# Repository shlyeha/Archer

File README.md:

# Nasty clock crack
Archer is a crack system for nasty gps-clock that makes it possible to 
sleep when you are on duty in a responsible position

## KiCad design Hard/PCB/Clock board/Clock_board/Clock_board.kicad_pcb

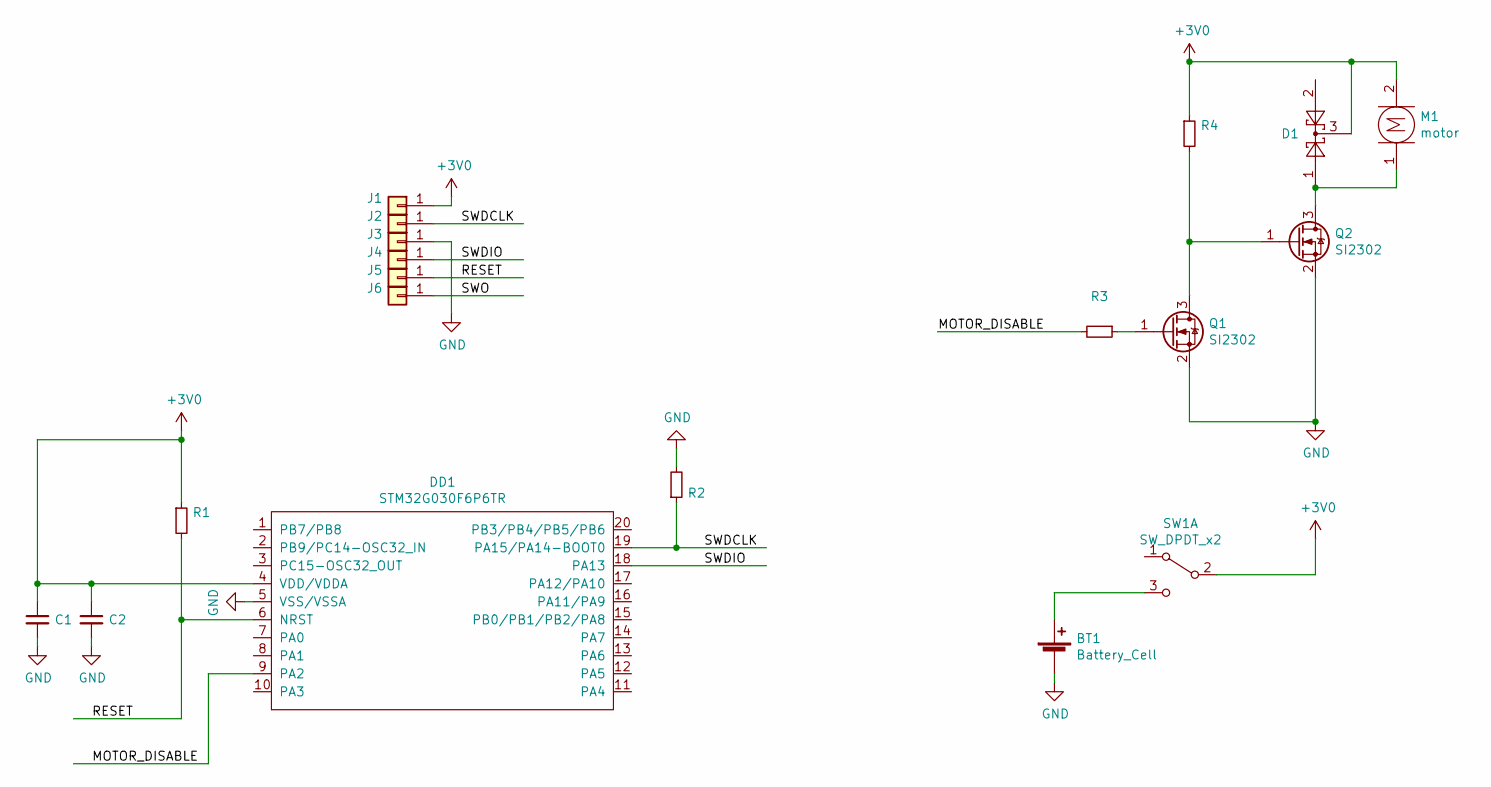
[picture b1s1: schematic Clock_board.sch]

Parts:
BT1: Battery_Cell; cr2032_holder
C1: CC0402KRX7R7BB104; C_0402_1005Metric
C2: CL05B105KQ5NQNC; C_0402_1005Metric
D1: BAT54C, 215; SOT-23
DD1: STM32G030F6P6TR; TSSOP-20_4.4x6.5mm_P0.65mm
J1, J2, J3, J4, J5, J6: Conn_01x01; custom_connector
M1: motor; motor_xiaomi_redmi_3s
Q1, Q2: SI2302; SOT-23
R1: RC0402JR-0710KL; R_0402_1005Metric
R2: 0805W8J0511T5E; R_0805_2012Metric
R3: MCR10ERTF2000; R_0805_2012Metric
R4: RMC080510M1%N; R_0805_2012Metric
SW1: SW_DPDT_x2; switch_ms-22c01

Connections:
+3V0: C1.1, C2.1, D1.3, DD1.4 (VDD/VDDA), J1.1, M1.2, R1.1, R4.1, SW1.2 (B)
/MOTOR_DISABLE: DD1.9 (PA2), R3.2
/RESET: DD1.6 (NRST), J5.1, R1.2
/SWDCLK: DD1.19 (PA15/PA14-BOOT0), J2.1, R2.1
/SWDIO: DD1.18 (PA13), J4.1
/SWO: J6.1
GND: BT1.2 (-), C1.2, C2.2, DD1.5 (VSS/VSSA), J3.1, Q1.2 (S), Q2.2 (S), R2.2
unnamed: BT1.1 (+), SW1.3 (C)
unnamed: D1.1, M1.1, Q2.3 (D)
unnamed: Q1.1 (G), R3.1
unnamed: Q1.3 (D), Q2.1 (G), R4.2

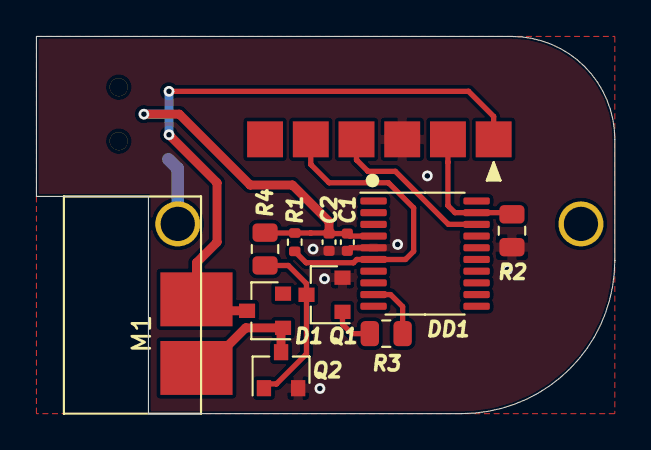
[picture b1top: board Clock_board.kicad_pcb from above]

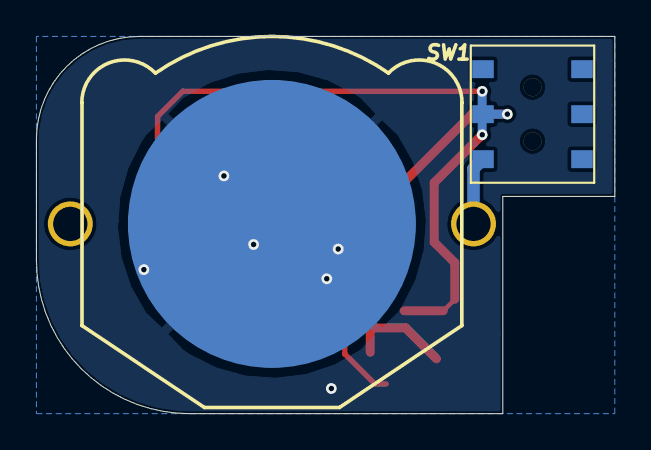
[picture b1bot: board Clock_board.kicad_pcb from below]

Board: 2 copper layers, 32.1 x 21.0 mm, 19 parts (2 on the bottom side), 10 nets.

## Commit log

2021-06-16 shlyeha added motor scheme simulation
2021-06-16 shlyeha changed load from resistor to switching inductor in simulation scheme, added 3D models and step files for cr2032 holder and motor, added kicad project and connectors, mechanical, stm32 librar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
2021-06-16 shlyeha added switch 3D model and step file
2021-06-16 shlyeha added switch component to mechanical library, changed scheme switch connection, finished pcb project
2021-06-16 shlyeha added motor holding polygon
2021-06-17 shlyeha added Details.txt file, defined components fields
2021-06-17 shlyeha added BOM file
2021-06-17 shlyeha changed pcb project files pathes
2021-06-17 shlyeha generated gerber files
2021-06-17 shlyeha added centroid file
2021-06-17 shlyeha added assembly images
